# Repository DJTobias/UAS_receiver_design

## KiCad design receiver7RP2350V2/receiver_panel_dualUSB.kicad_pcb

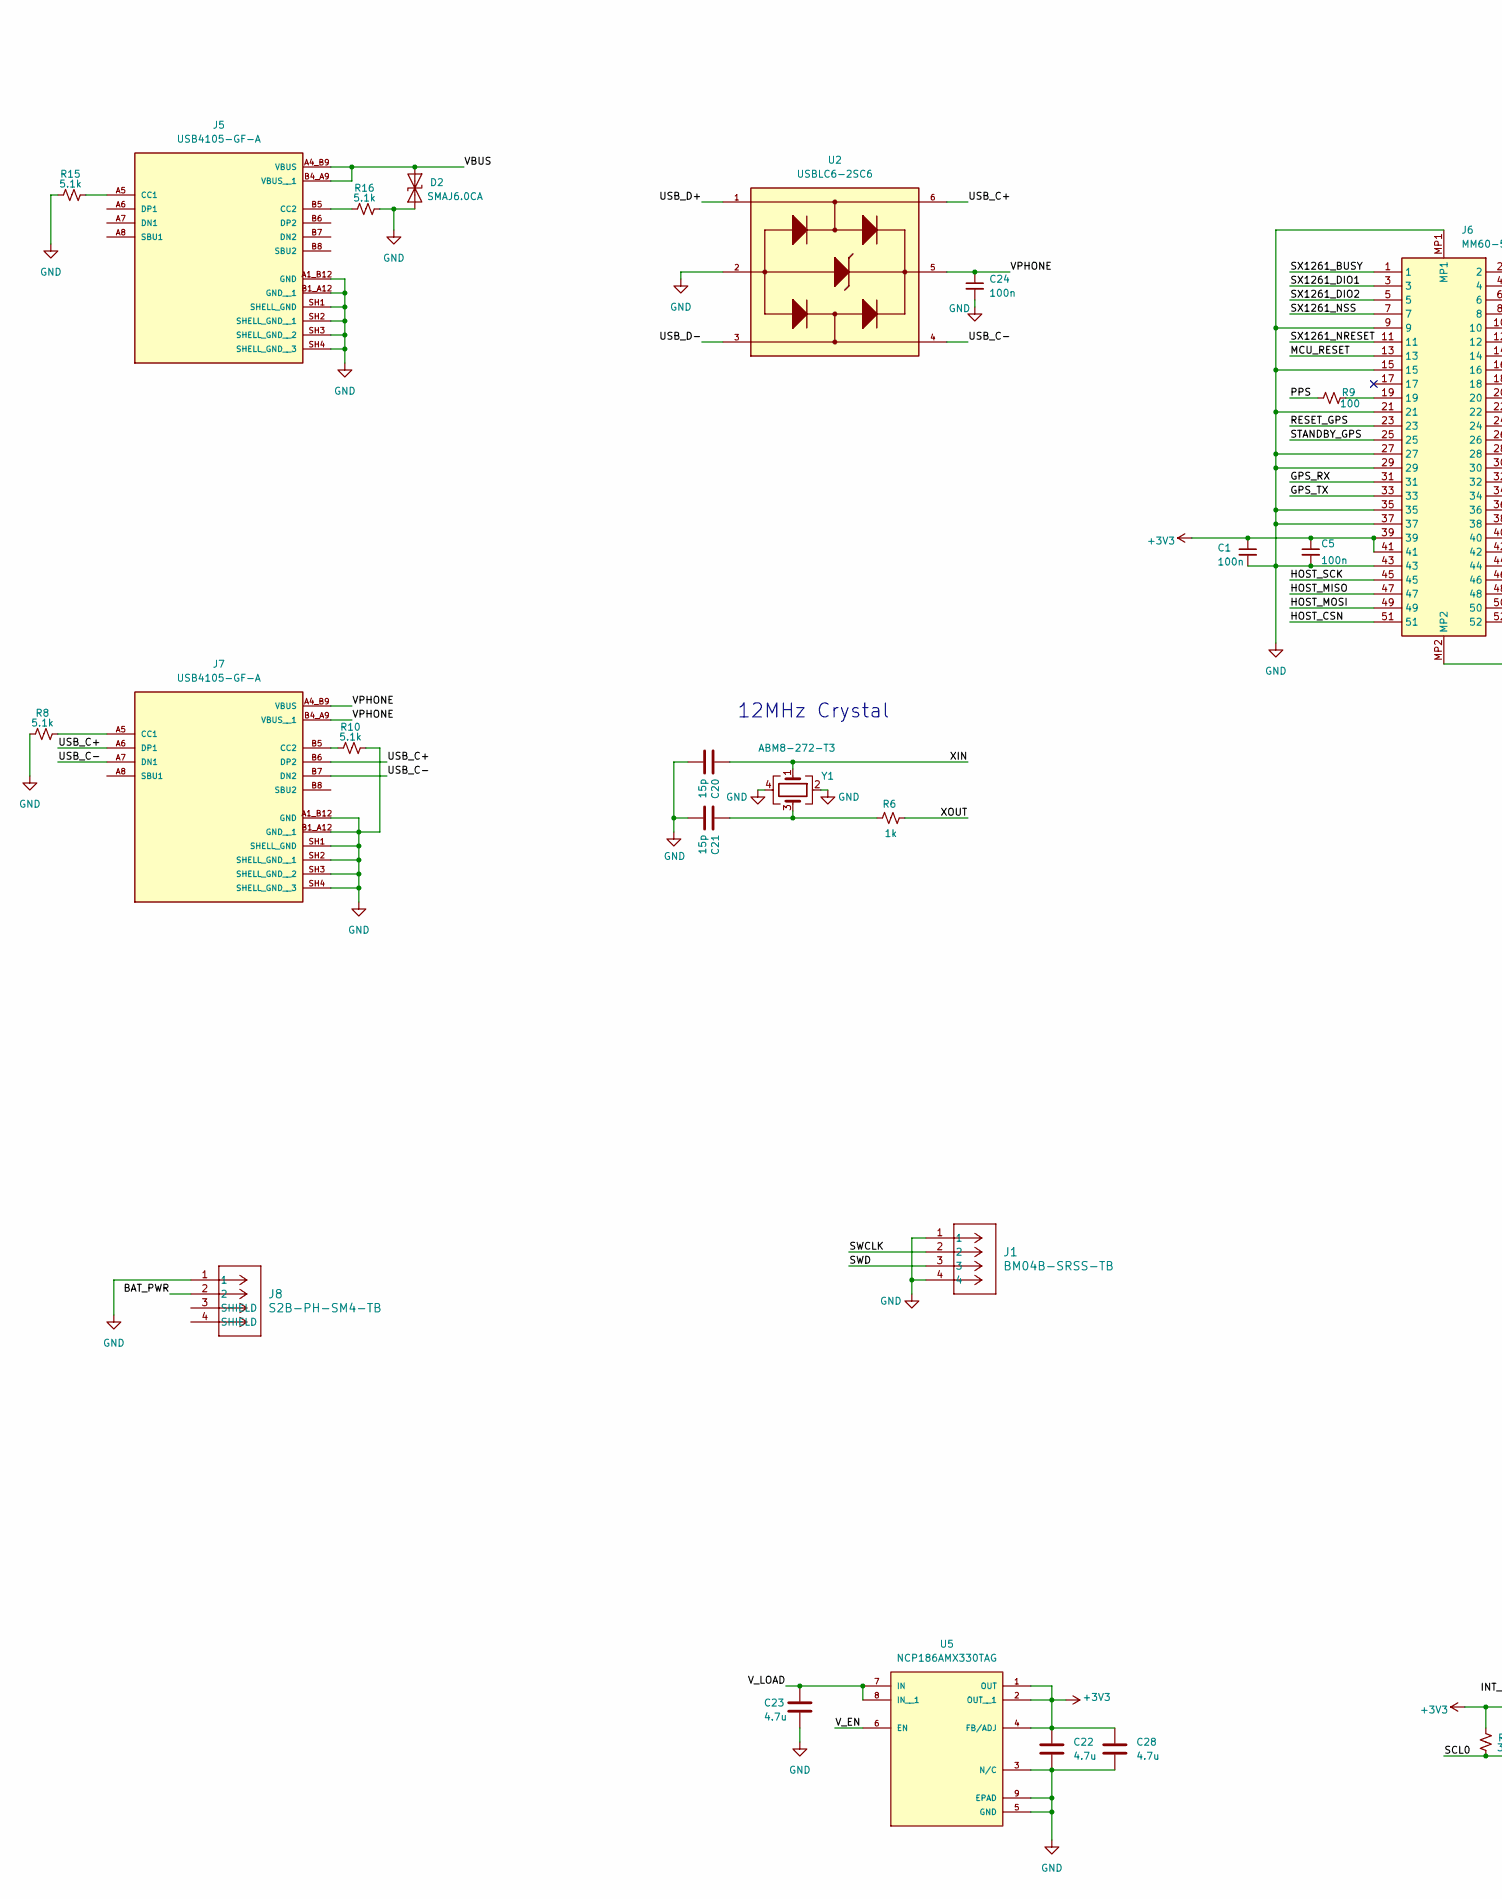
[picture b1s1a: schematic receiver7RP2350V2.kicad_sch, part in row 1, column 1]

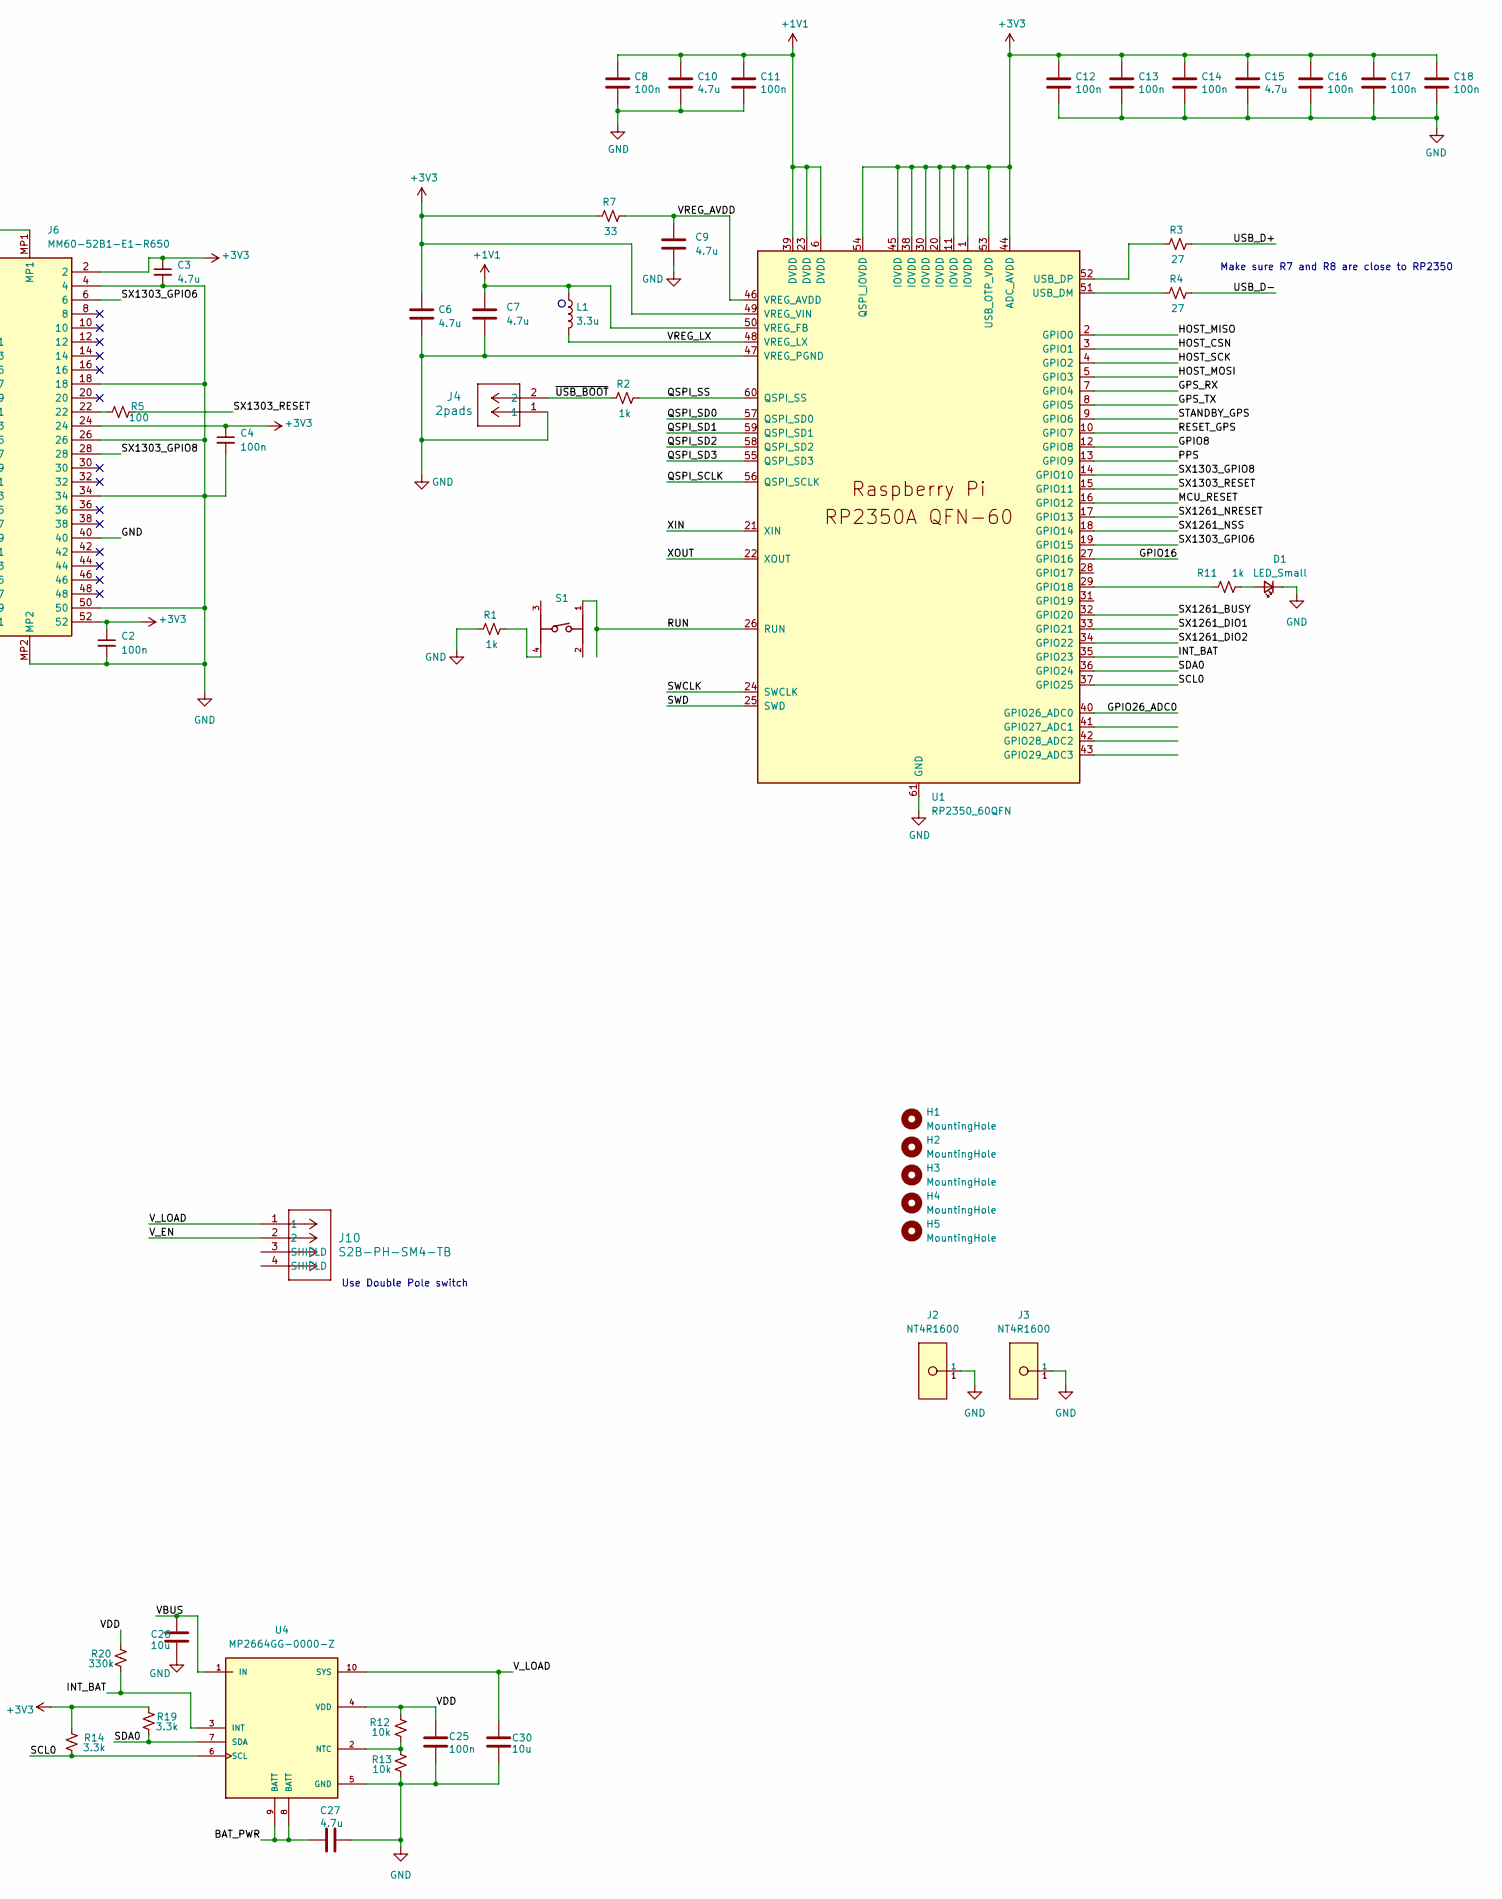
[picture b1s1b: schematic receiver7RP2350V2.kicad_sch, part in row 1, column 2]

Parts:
C1, C2, C4, C5, C8, C11, C12, C13, C14, C16, C17, C18, C24, C25: 100n; C_0402_1005Metric
C3, C9, C10, C15, C22, C23, C27, C28: 4.7u; C_0402_1005Metric
C6, C7: 4.7u; C_0402_1005Metric_small_pads
C20, C21: 15p; C_0402_1005Metric
C26, C30: 10u; C_0805_2012Metric
D1: LED_Small; LED_0402_1005Metric
D2: SMAJ6.0CA; D_SMA
H1: MountingHole; MountingHole_2.5mm
H2, H3, H4, H5: MountingHole; MountingHole_2.7mm_M2.5_Pad_Via
J1: BM04B-SRSS-TB; CONN4_BM04B-SRSS_JST
J2, J3: NT4R1600; JAE_Electronics-NT4R1600-MFG; mouser part number 656-NT4R1600; digikey description STANDOFF FOR MM60 SERIES
J4: 2pads; 2pin pad_larger
J5, J7: USB4105-GF-A; GCT_USB4105-GF-A; PARTREV B4
J6: MM60-52B1-E1-R650; MM6052B1E1R650_mod_screw; Mouser Part Number 656-MM60-52B1-E1-R
J8, J10: S2B-PH-SM4-TB; CONN_S2B-PH-SM4-TB_JST_mod2
L1: 3.3u; L_pol_2016
R1, R2, R6, R11: 1k; R_0402_1005Metric
R3, R4: 27; R_0402_1005Metric
R5, R9: 100; R_0402_1005Metric
R7: 33; R_0402_1005Metric
R8, R10, R15, R16: 5.1k; R_0402_1005Metric
R12, R13: 10k; R_0402_1005Metric
R14, R19: 3.3k; R_0402_1005Metric
R20: 330k; R_0402_1005Metric
S1: 434133025816; 434133025816_mod
U1: RP2350_60QFN; RP2350-QFN-60-1EP_7x7_P0.4mm_EP3.4x3.4mm_ThermalVias
U2: USBLC6-2SC6; SOT95P280X145-6N
U4: MP2664GG-0000-Z; QFN50P200X200X105-10N; PARTREV 1.01
U5: NCP186AMX330TAG; PSON40P160X120X45-9N; PARTREV Rev.5
Y1: ABM8-272-T3; Crystal_SMD_3225-4Pin_3.2x2.5mm

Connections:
Board_0-+1V1: C7.1, C8.1, C10.1, C11.1, L1.1, U1.6 (DVDD), U1.23 (DVDD), U1.39 (DVDD), U1.50 (VREG_FB)
Board_0-+3V3: C1.1, C2.1, C3.1, C4.1, C5.1, C6.1, C12.1, C13.1, C14.1, C15.1, C16.1, C17.1, C18.1, C22.1, C28.1, J6.2, J6.24, J6.39, J6.41, J6.52, R7.1, R14.2, R19.2, U1.1 (IOVDD), U1.11 (IOVDD), U1.20 (IOVDD), U1.30 (IOVDD), U1.38 (IOVDD), U1.44 (ADC_AVDD), U1.45 (IOVDD), U1.49 (VREG_VIN), U1.53 (USB_OTP_VDD), U1.54 (QSPI_IOVDD), U5.1 (OUT), U5.2 (OUT__1), U5.4 (FB/ADJ)
Board_0-/BAT_PWR: C27.1, J8.2, U4.8 (BATT), U4.9 (BATT)
Board_0-/GPIO8: U1.12 (GPIO8)
Board_0-/GPIO16: U1.27 (GPIO16)
Board_0-/GPIO26_ADC0: U1.40 (GPIO26_ADC0)
Board_0-/GPS_RX: J6.31, U1.7 (GPIO4)
Board_0-/GPS_TX: J6.33, U1.8 (GPIO5)
Board_0-/HOST_CSN: J6.51, U1.3 (GPIO1)
Board_0-/HOST_MISO: J6.47, U1.2 (GPIO0)
Board_0-/HOST_MOSI: J6.49, U1.5 (GPIO3)
Board_0-/HOST_SCK: J6.45, U1.4 (GPIO2)
Board_0-/INT_BAT: R20.1, U1.35 (GPIO23), U4.3 (INT)
Board_0-/MCU_RESET: J6.13, U1.16 (GPIO12)
Board_0-/PPS: R9.1, U1.13 (GPIO9)
Board_0-/QSPI_SCLK: U1.56 (QSPI_SCLK)
Board_0-/QSPI_SD0: U1.57 (QSPI_SD0)
Board_0-/QSPI_SD1: U1.59 (QSPI_SD1)
Board_0-/QSPI_SD2: U1.58 (QSPI_SD2)
Board_0-/QSPI_SD3: U1.55 (QSPI_SD3)
Board_0-/QSPI_SS: R2.2, U1.60 (QSPI_SS)
Board_0-/RESET_GPS: J6.23, U1.10 (GPIO7)
Board_0-/RUN: S1.1, U1.26 (RUN)
Board_0-/SCL0: R14.1, U1.37 (GPIO25), U4.6 (SCL)
Board_0-/SDA0: R19.1, U1.36 (GPIO24), U4.7 (SDA)
Board_0-/STANDBY_GPS: J6.25, U1.9 (GPIO6)
Board_0-/SWCLK: J1.2, U1.24 (SWCLK)
Board_0-/SWD: J1.3, U1.25 (SWD)
Board_0-/SX1261_BUSY: J6.1, U1.32 (GPIO20)
Board_0-/SX1261_DIO1: J6.3, U1.33 (GPIO21)
Board_0-/SX1261_DIO2: J6.5, U1.34 (GPIO22)
Board_0-/SX1261_NRESET: J6.11, U1.17 (GPIO13)
Board_0-/SX1261_NSS: J6.7, U1.18 (GPIO14)
Board_0-/SX1303_GPIO6: J6.6, U1.19 (GPIO15)
Board_0-/SX1303_GPIO8: J6.28, U1.14 (GPIO10)
Board_0-/SX1303_RESET: R5.2, U1.15 (GPIO11)
Board_0-/USB_C+: J7.A6 (DP1), J7.B6 (DP2), U2.6
Board_0-/USB_C-: J7.A7 (DN1), J7.B7 (DN2), U2.4
Board_0-/USB_D+: R3.2, U2.1
Board_0-/USB_D-: R4.2, U2.3
Board_0-/VBUS: C26.1, D2.2 (A2), J5.A4_B9 (VBUS), J5.B4_A9 (VBUS__1), U4.1 (IN)
Board_0-/VDD: C25.1, R12.2, R20.2, U4.4 (VDD)
Board_0-/VPHONE: C24.1, J7.A4_B9 (VBUS), J7.B4_A9 (VBUS__1), U2.5
Board_0-/VREG_AVDD: C9.1, R7.2, U1.46 (VREG_AVDD)
Board_0-/VREG_LX: L1.2, U1.48 (VREG_LX)
Board_0-/V_EN: J10.2, U5.6 (EN)
Board_0-/V_LOAD: C23.1, C30.1, J10.1, U4.10 (SYS), U5.7 (IN), U5.8 (IN__1)
Board_0-/XIN: C20.1, U1.21 (XIN), Y1.1
Board_0-/XOUT: R6.2, U1.22 (XOUT)
Board_0-/~USB_BOOT: J4.2, R2.1
Board_0-GND: C1.2, C2.2, C3.2, C4.2, C5.2, C6.2, C7.2, C8.2, C9.2, C10.2, C11.2, C12.2, C13.2, C14.2, C15.2, C16.2, C17.2, C18.2, C20.2, C21.2, C22.2, C23.2, C24.2, C25.2, C26.2, C27.2, C28.2, C30.2, D1.1 (K), D2.1 (A1), J1.1, J1.4, J2.1, J3.1, J4.1, J5.A1_B12 (GND), J5.B1_A12 (GND__1), J5.SH1 (SHELL_GND), J5.SH2 (SHELL_GND__1), J5.SH3 (SHELL_GND__2), J5.SH4 (SHELL_GND__3), J6.4, J6.9, J6.15, J6.18, J6.21, J6.26, J6.27, J6.29, J6.34, J6.35, J6.37, J6.40, J6.43, J6.50, J6.MP1, J6.MP2, J7.A1_B12 (GND), J7.B1_A12 (GND__1), J7.SH1 (SHELL_GND), J7.SH2 (SHELL_GND__1), J7.SH3 (SHELL_GND__2), J7.SH4 (SHELL_GND__3), J8.1, R1.1, R8.1, R10.2, R13.1, R15.1, R16.2, U1.47 (VREG_PGND), U1.61 (GND), U2.2, U4.5 (GND), U5.3 (N/C), U5.5 (GND), U5.9 (EPAD), Y1.2, Y1.4
Board_0-Net-(C21-Pad1): C21.1, R6.1, Y1.3
Board_0-Net-(D1-A): D1.2 (A), R11.2
Board_0-Net-(J5-CC1): J5.A5 (CC1), R15.2
Board_0-Net-(J5-CC2): J5.B5 (CC2), R16.1
Board_0-Net-(J6-Pad19): J6.19, R9.2
Board_0-Net-(J6-Pad22): J6.22, R5.1
Board_0-Net-(J7-CC1): J7.A5 (CC1), R8.2
Board_0-Net-(J7-CC2): J7.B5 (CC2), R10.1
Board_0-Net-(R1-Pad2): R1.2, S1.4
Board_0-Net-(U1-GPIO18): R11.1, U1.29 (GPIO18)
Board_0-Net-(U1-USB_DM): R4.1, U1.51 (USB_DM)
Board_0-Net-(U1-USB_DP): R3.1, U1.52 (USB_DP)
Board_0-Net-(U4-NTC): R12.1, R13.2, U4.2 (NTC)
Board_0-unconnected-(J5-DN1-PadA7): J5.A7 (DN1)
Board_0-unconnected-(J5-DN2-PadB7): J5.B7 (DN2)
Board_0-unconnected-(J5-DP1-PadA6): J5.A6 (DP1)
Board_0-unconnected-(J5-DP2-PadB6): J5.B6 (DP2)
Board_0-unconnected-(J5-SBU1-PadA8): J5.A8 (SBU1)
Board_0-unconnected-(J5-SBU2-PadB8): J5.B8 (SBU2)
Board_0-unconnected-(J6-Pad8): J6.8
Board_0-unconnected-(J6-Pad10): J6.10
Board_0-unconnected-(J6-Pad12): J6.12
Board_0-unconnected-(J6-Pad14): J6.14
Board_0-unconnected-(J6-Pad16): J6.16
Board_0-unconnected-(J6-Pad17): J6.17
Board_0-unconnected-(J6-Pad20): J6.20
Board_0-unconnected-(J6-Pad30): J6.30
Board_0-unconnected-(J6-Pad32): J6.32
Board_0-unconnected-(J6-Pad36): J6.36
Board_0-unconnected-(J6-Pad38): J6.38
Board_0-unconnected-(J6-Pad42): J6.42
Board_0-unconnected-(J6-Pad44): J6.44
Board_0-unconnected-(J6-Pad46): J6.46
Board_0-unconnected-(J6-Pad48): J6.48
Board_0-unconnected-(J7-SBU1-PadA8): J7.A8 (SBU1)
Board_0-unconnected-(J7-SBU2-PadB8): J7.B8 (SBU2)
Board_0-unconnected-(J8-SHIELD-Pad3): J8.3 (SHIELD)
Board_0-unconnected-(J8-SHIELD-Pad4): J8.4 (SHIELD)
Board_0-unconnected-(J10-SHIELD-Pad3): J10.3 (SHIELD)
Board_0-unconnected-(J10-SHIELD-Pad4): J10.4 (SHIELD)
Board_0-unconnected-(S1-Pad2): S1.2
Board_0-unconnected-(S1-Pad3): S1.3
Board_0-unconnected-(U1-GPIO17-Pad28): U1.28 (GPIO17)
Board_0-unconnected-(U1-GPIO19-Pad31): U1.31 (GPIO19)
Board_0-unconnected-(U1-GPIO27_ADC1-Pad41): U1.41 (GPIO27_ADC1)
Board_0-unconnected-(U1-GPIO28_ADC2-Pad42): U1.42 (GPIO28_ADC2)
Board_0-unconnected-(U1-GPIO29_ADC3-Pad43): U1.43 (GPIO29_ADC3)

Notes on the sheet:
Use Double Pole switch
12MHz Crystal
Make sure R7 and R8 are close to RP2350

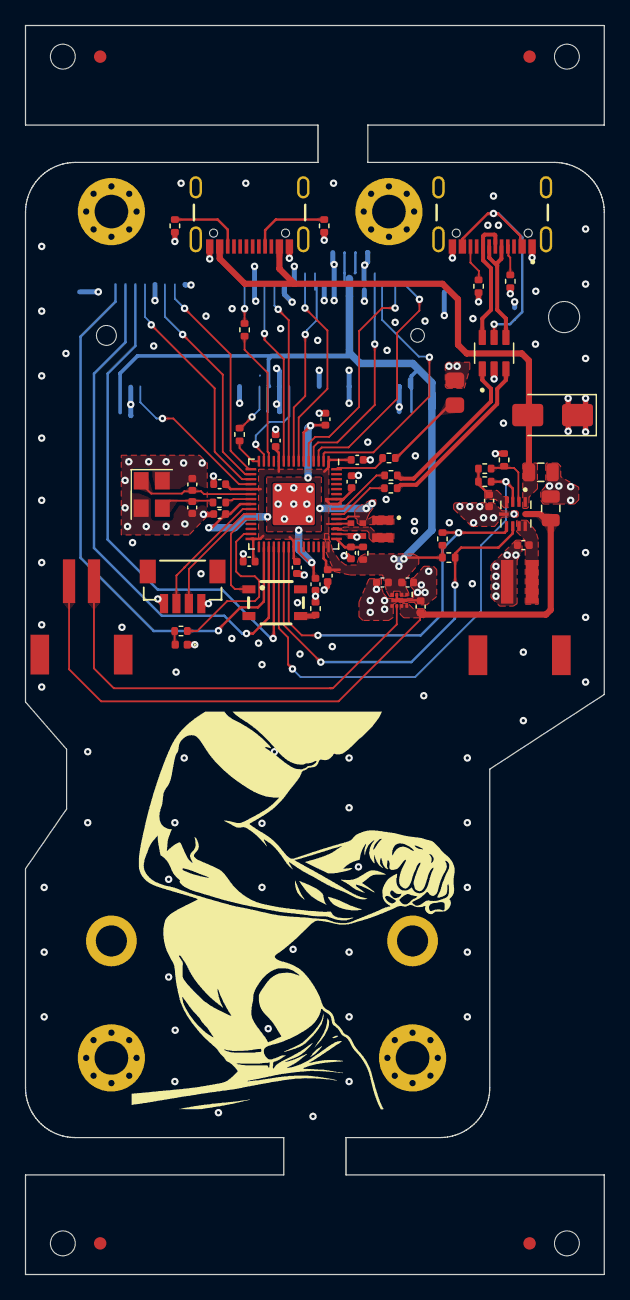
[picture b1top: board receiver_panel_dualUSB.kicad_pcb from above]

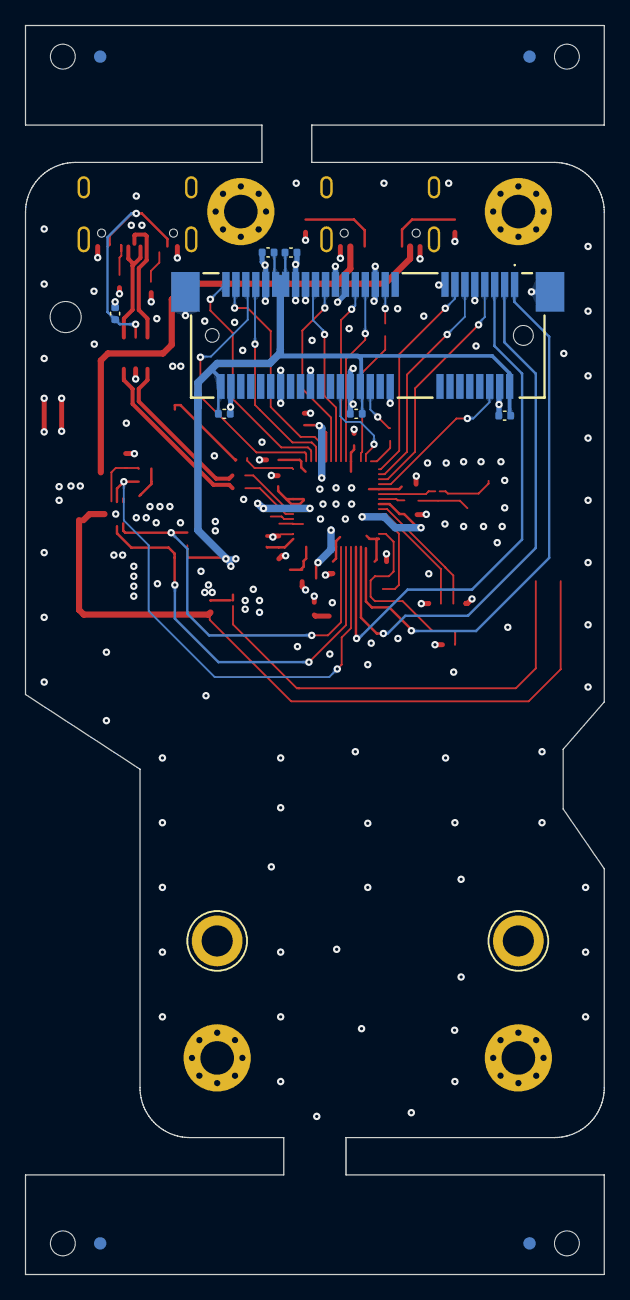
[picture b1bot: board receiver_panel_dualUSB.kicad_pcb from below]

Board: 4 copper layers, 46.5 x 100.4 mm, 81 parts (13 on the bottom side), 56 nets.

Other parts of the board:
KiKit_FID_B_1, KiKit_FID_B_2, KiKit_FID_B_3, KiKit_FID_B_4: Fiducial
KiKit_FID_T_1, KiKit_FID_T_2, KiKit_FID_T_3, KiKit_FID_T_4: Fiducial
KiKit_TO_1, KiKit_TO_2, KiKit_TO_3, KiKit_TO_4: NPTH

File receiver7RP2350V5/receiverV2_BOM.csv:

"Reference","Value","Datasheet","Footprint","Qty","DNP"
"C1,C2,C4,C5,C8,C11,C12,C13,C14,C16,C17,C18,C24,C25","100n","~","Capacitor_SMD:C_0402_1005Metric","14",""
"C3,C6,C7,C9,C10,C15,C27","4.7u","~","Capacitor_SMD:C_0402_1005Metric,RP2350_60QFN_minimal:C_0402_1005Metric_small_pads","7",""
"C19,C22,C23,C26,C30","10u","~","Capacitor_SMD:C_0805_2012Metric","5",""
"C20,C21","15p","~","Capacitor_SMD:C_0402_1005Metric","2",""
"D1","LED_Small","~","LED_SMD:LED_0402_1005Metric","1",""
"J1","BM04B-SRSS-TB","BM04B-SRSS-TB","BM04B_SRSS_TB:CONN4_BM04B-SRSS_JST","1",""
"J2,J3","NT4R1600","https://www.jae.com/en/connectors/series/detail/product/id=68912","NT4R1600:JAE_Electronics-NT4R1600-MFG","2",""
"J4","2pads","S3B-PH-SM4-TB","PADS:2pin pad_larger","1",""
"J6","MM60-52B1-E1-R650","https://www.mouser.in/datasheet/2/206/JAEIS03536_1-2550299.pdf","MM60-52B1-E1-R650:MM6052B1E1R650_mod_screw","1",""
"J7","USB4105-GF-A","","USB4105_GF_A:GCT_USB4105-GF-A","1",""
"J8,J10","S2B-PH-SM4-TB","S2B-PH-SM4-TB","JST2pin:CONN_S2B-PH-SM4-TB_JST_mod2","2",""
"L1","3.3u","~","RP2350_60QFN_minimal:L_pol_2016","1",""
"R1,R2,R6,R11","1k","~","Resistor_SMD:R_0402_1005Metric","4",""
"R3,R4","27","~","Resistor_SMD:R_0402_1005Metric","2",""
"R5,R9","100","~","Resistor_SMD:R_0402_1005Metric","2",""
"R7","33","~","Resistor_SMD:R_0402_1005Metric","1",""
"R8,R10","5.1k","~","Resistor_SMD:R_0402_1005Metric","2",""
"R12,R13","10k","~","Resistor_SMD:R_0402_1005Metric","2",""
"R14,R19","3.3k","~","Resistor_SMD:R_0402_1005Metric","2",""
"R15","100k","~","Resistor_SMD:R_0402_1005Metric","1",""
"R20","300k","~","Resistor_SMD:R_0402_1005Metric","1",""
"S1","434133025816","","434133025816:434133025816_mod","1",""
"U1","RP2350_60QFN","","RP2350_60QFN_minimal:RP2350-QFN-60-1EP_7x7_P0.4mm_EP3.4x3.4mm_ThermalVias","1",""
"U2","USBLC6-2SC6","","USBLC6_2SC6:SOT95P280X145-6N","1",""
"U3","AP7361C-33Y5-13","AP7361C-33Y5-13","AP7361C_33Y5_13:SOT89-5_DIO-M_MODGND","1",""
"U4","MP2664GG-0000-Z","","MP2664GG-0000-Z:QFN50P200X200X105-10N","1",""
"Y1","ABM8-272-T3","~","adafruit:Crystal_SMD_3225-4Pin_3.2x2.5mm","1",""

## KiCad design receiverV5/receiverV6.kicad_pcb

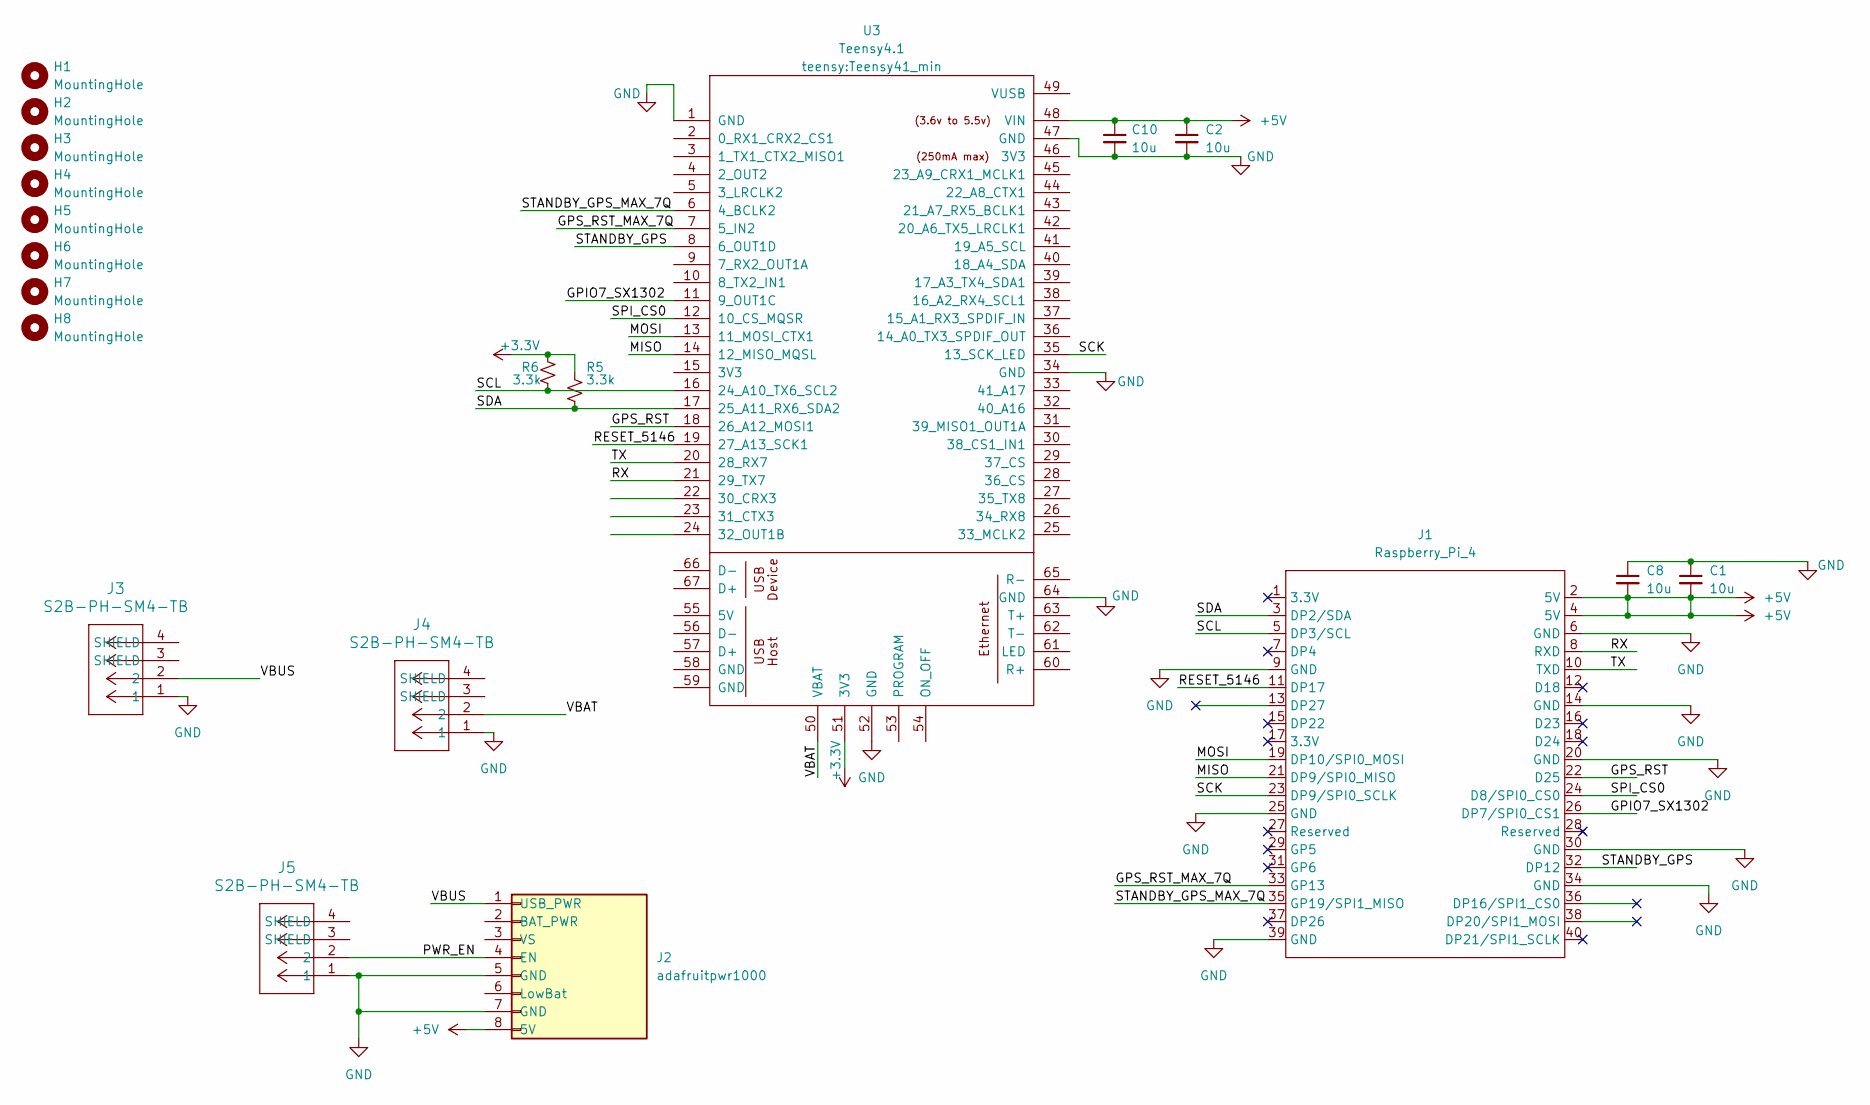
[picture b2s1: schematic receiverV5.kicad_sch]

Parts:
C1, C2, C8, C10: 10u; C_1206_3216Metric_Pad1.33x1.80mm_HandSolder
H1, H2, H3, H4: MountingHole; mountinghole3mm
H5: MountingHole; MountingHole_4mm_t4
H6, H7, H8: MountingHole; mountinghole4mm
J1: Raspberry_Pi_4; PinHeader_2x20_P2.54mm_Vertical
J2: adafruitpwr1000; adafruit powerboost 1000
J3, J4, J5: S2B-PH-SM4-TB; CONN_S2B-PH-SM4-TB_JST_mod2
R5, R6: 3.3k; R_1206_3216Metric_Pad1.30x1.75mm_HandSolder
U3: Teensy4.1; Teensy41_min

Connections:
+3.3V: R5.1, R6.1, U3.51 (3V3)
+5V: C1.2, C2.1, C8.2, C10.1, J1.2 (5V), J1.4 (5V), J2.8 (5V), U3.48 (VIN)
/GPIO7_SX1302: J1.26 (DP7/SPI0_CS1), U3.11 (9_OUT1C)
/GPS_RST: J1.22 (D25), U3.18 (26_A12_MOSI1)
/GPS_RST_MAX_7Q: J1.33 (GP13), U3.7 (5_IN2)
/MISO: J1.21 (DP9/SPI0_MISO), U3.14 (12_MISO_MQSL)
/MOSI: J1.19 (DP10/SPI0_MOSI), U3.13 (11_MOSI_CTX1)
/PWR_EN: J2.4 (EN), J5.2
/RESET_5146: J1.11 (DP17), U3.19 (27_A13_SCK1)
/RX: J1.8 (RXD), U3.21 (29_TX7)
/SCK: J1.23 (DP9/SPI0_SCLK), U3.35 (13_SCK_LED)
/SCL: J1.5 (DP3/SCL), R6.2, U3.16 (24_A10_TX6_SCL2)
/SDA: J1.3 (DP2/SDA), R5.2, U3.17 (25_A11_RX6_SDA2)
/SPI_CS0: J1.24 (D8/SPI0_CS0), U3.12 (10_CS_MQSR)
/STANDBY_GPS: J1.32 (DP12), U3.8 (6_OUT1D)
/STANDBY_GPS_MAX_7Q: J1.35 (GP19/SPI1_MISO), U3.6 (4_BCLK2)
/TX: J1.10 (TXD), U3.20 (28_RX7)
/VBAT: J4.2, U3.50 (VBAT)
/VBUS: J2.1 (USB_PWR), J3.2
GND: C1.1, C2.2, C8.1, C10.2, J1.6 (GND), J1.9 (GND), J1.14 (GND), J1.20 (GND), J1.25 (GND), J1.30 (GND), J1.34 (GND), J1.39 (GND), J2.5 (GND), J2.7 (GND), J3.1, J4.1, J5.1, U3.1 (GND), U3.34 (GND), U3.47 (GND), U3.52 (GND), U3.64 (GND)

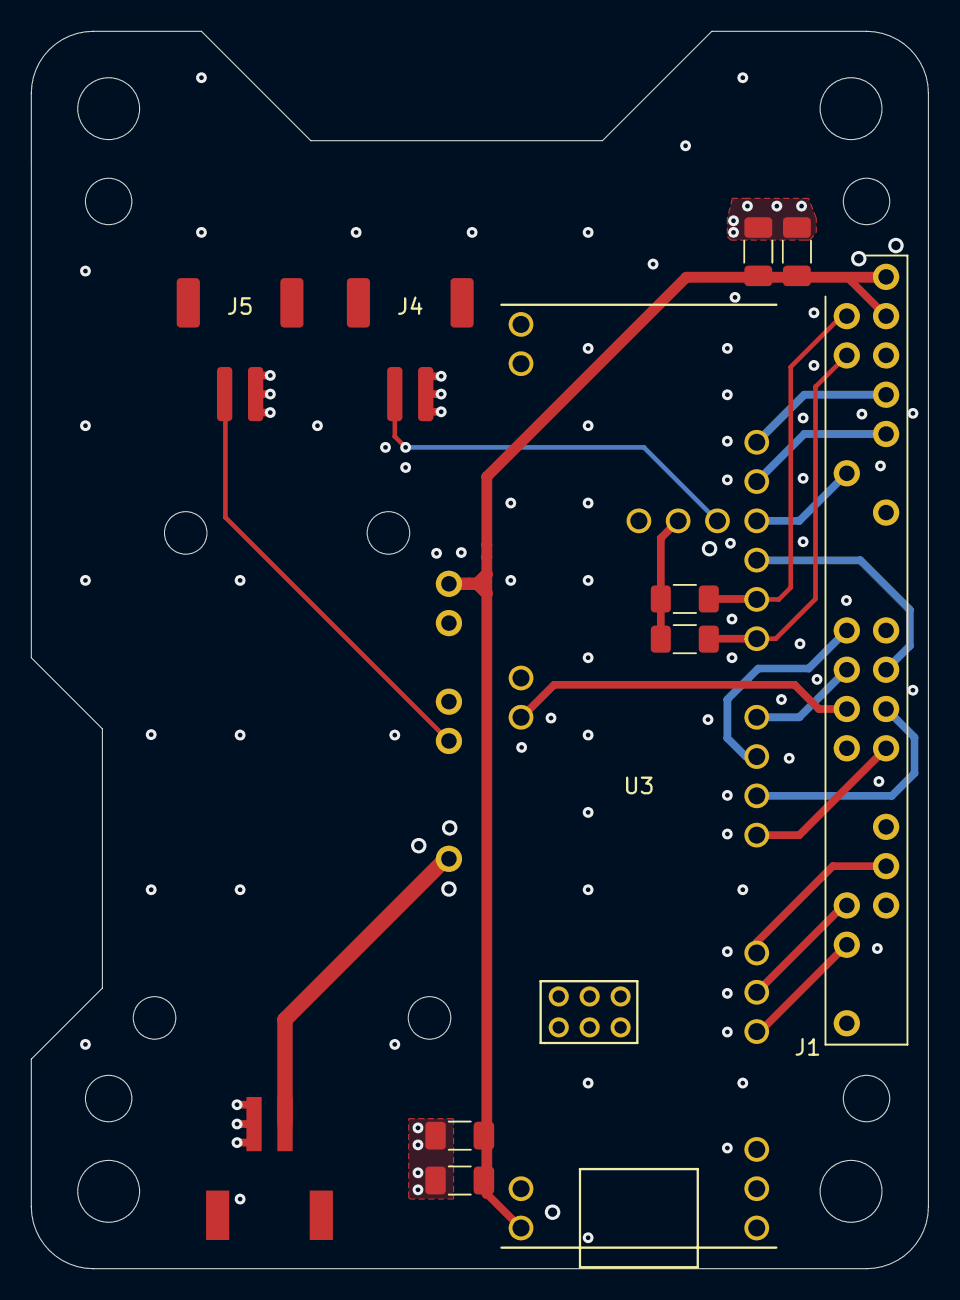
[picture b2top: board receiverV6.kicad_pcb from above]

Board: 4 copper layers, 58.0 x 80.0 mm, 20 parts (0 on the bottom side), 20 nets.
